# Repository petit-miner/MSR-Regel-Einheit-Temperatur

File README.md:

# MSR-Regel-Einheit-Temperatur
Dieses Projekt entstand in der Technik / µC AG des CRBK. Die Aufgabe war es die Temperatur eines Schaltschrankes zu überwachen und ggf. mit einem Lüfter zu kühlen. <br>
Diese Platine bietet die Möglichkeit die gemessen Temperaturen auf einer micro SD Karte zu loggen und auch per Ethernet entweder als Webserver oder als Client die gemessenen Daten bereitzustellen.<br> Die RTC sorgt beim Loggen für eine ständig korrekte Zeit.<br>
Es können bis zu 8 Onewire Sensoren, 3 PC-Lüfter und 2 normale Lüfter an die Platine angeschlossen werden.
<br>
<br>
Die Gerber Dateien und der Schaltplan wurden unter der Open Source Hardware Lizenz veröffentlicht und dürfen für den nicht kommerziellen Zweck gerne weiter verwendet werden.
<br>
<br>
Dieses Projekt wurde von Marcel Thürmer, Justin Wellenberg, Julian Prochowicz und Till Flesch entwickelt.

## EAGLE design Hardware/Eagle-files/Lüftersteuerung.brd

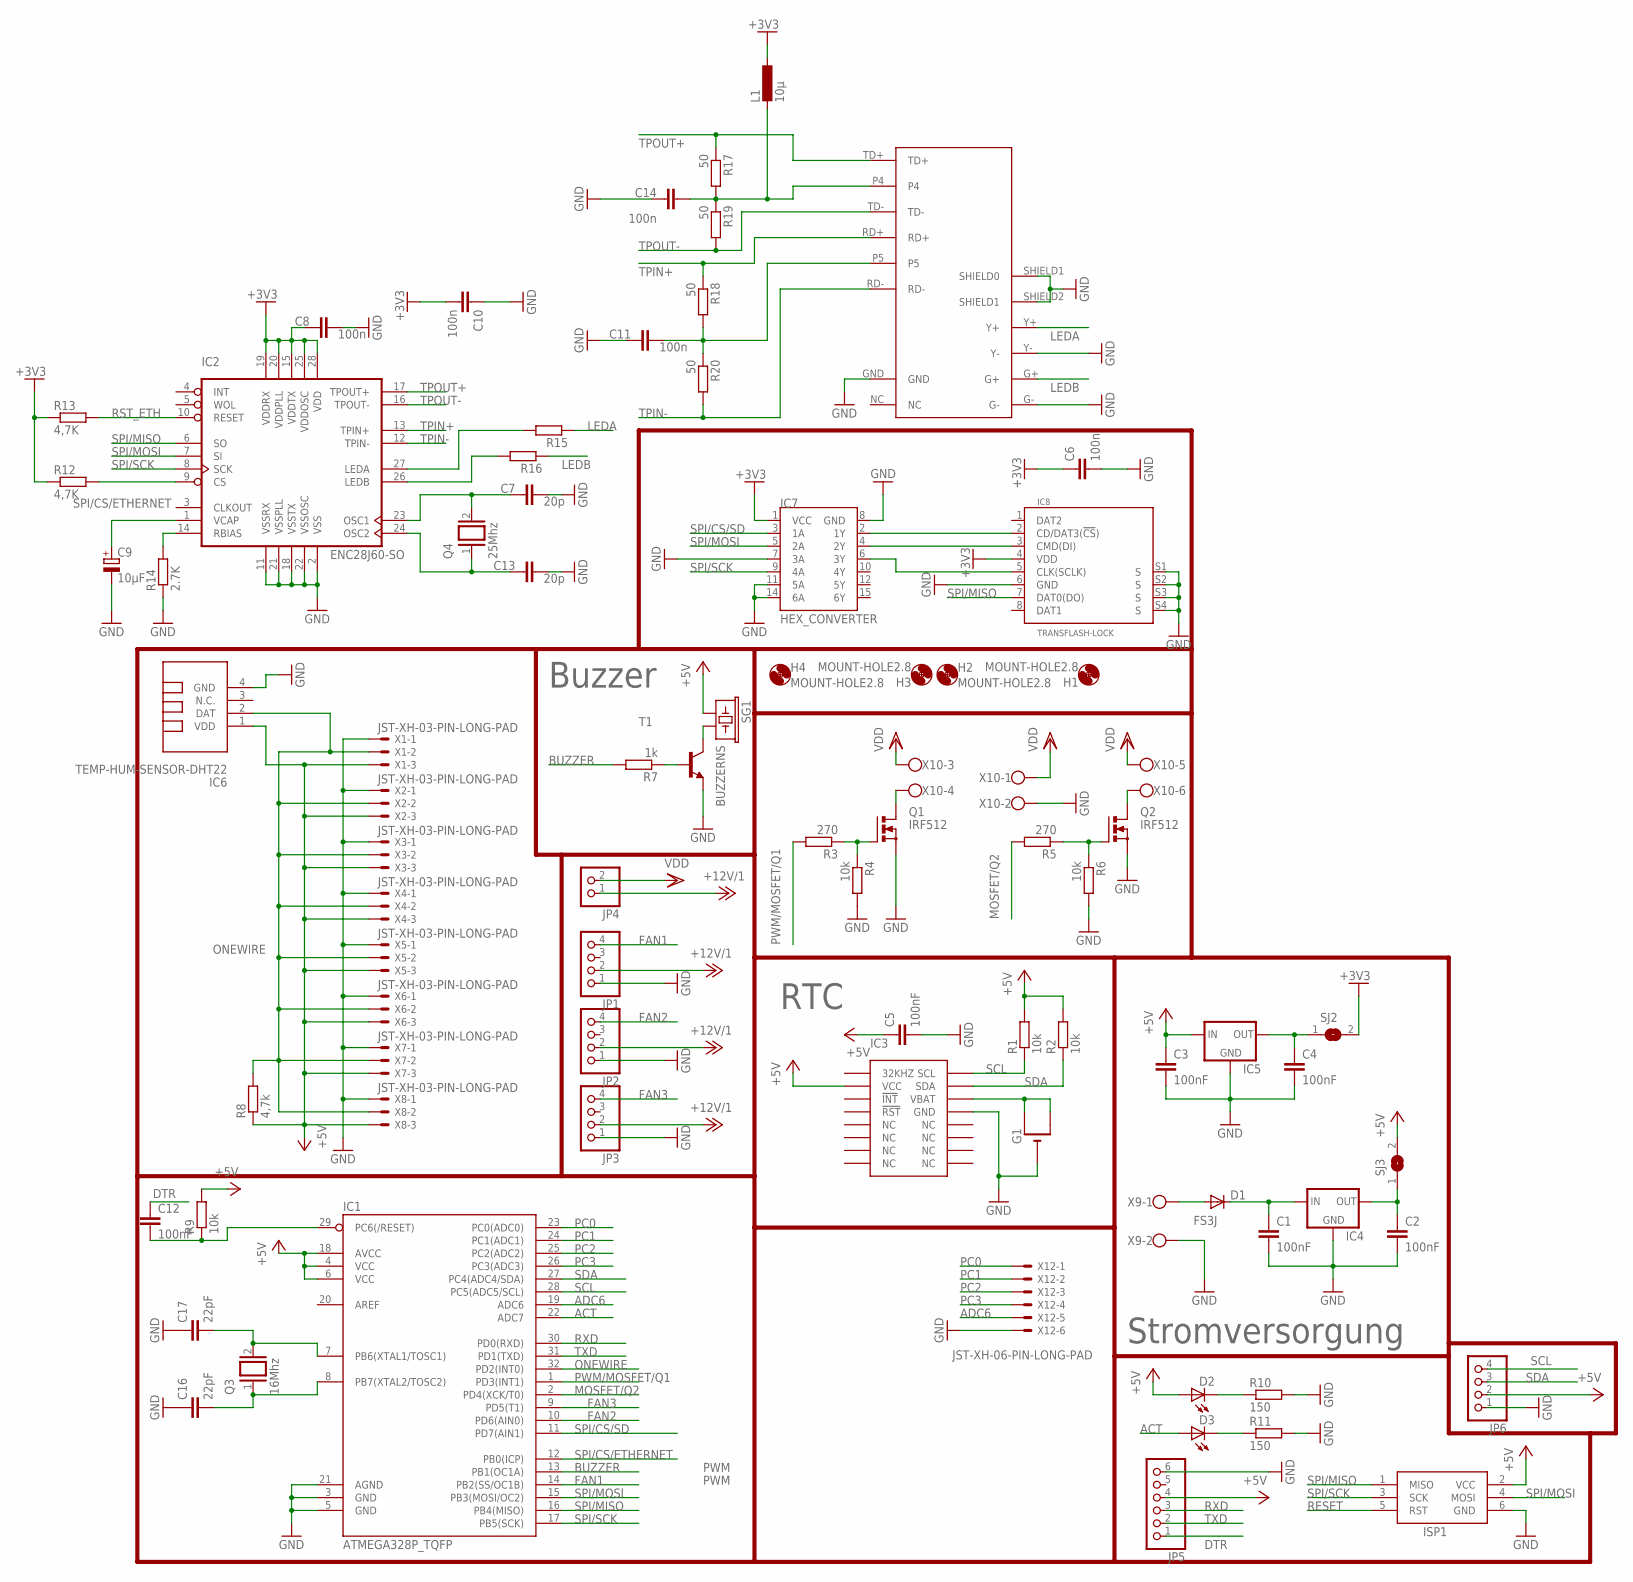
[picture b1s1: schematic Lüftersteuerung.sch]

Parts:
C1, C2, C3, C4, C5: 100nF; C1206
C6, C8, C10, C11, C14: 100n; C1206
C7, C13: 20p; C1206
C9: 10µF; A/3216-18W
C12: 100nF; C1206K
C16, C17: 22pF; C1206K
D1: FS3J; SMC
D2, D3: LED3MM
G1: CR1220SMT; CR1220-SMD
H1, H2, H3, H4: MOUNT-HOLE2.8; 2,8
IC1: ATMEGA328P_TQFP; TQFP32-08
IC2: ENC28J60-SO; SO28W
IC3: DS3231SOIC-16W; SOIC-16W
IC4, IC5: LM1117; SOT223
IC6: TEMP-HUM-SENSOR-DHT22
IC7: HEX_CONVERTER; SO016
IC8: TRANSFLASH-LOCK; TRANSFLASH-LOCK-SOCK
ISP1: AVRISP-6; AVRISP
JP1, JP2, JP3, JP6: PINHD-1X4; 1X04
JP4: PINHD-1X2; 1X02
JP5: PINHD-1X6; 1X06
L1: 10µ; L0805
Q1, Q2: IRF512; TO220BV
Q3: 16Mhz; QS
Q4: 25Mhz; QS
R1, R2, R4, R6: 10k; R1206
R3, R5: 270; R1206
R7: 1k; R1206
R8: 4,7k; R1206
R9: 10k; M1206
R10, R11: 150; M1206
R12, R13: 4,7K; R1206
R14: 2.7K; R1206
R15, R16: R-EU_R1206; R1206
R17, R18, R19, R20: 50; R1206
SG1: BUZZERNS; BUZZER-12MM-NS
SJ2, SJ3: SJ
T1: BC817-16-NPN-SOT23-BEC; SOT23-BEC
U$1: HR911105A; RJ45
X1, X2, X3, X4, X5, X6, X7, X8: JST-XH-03-PIN-LONG-PAD; JST-XH-03-PACKAGE-LONG-PAD
X9: W237-102
X10: W237-6
X12: JST-XH-06-PIN-LONG-PAD; JST-XH-06-PACKAGE-LONG-PAD

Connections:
+3V3: C6.1, C8.1, C10.2, IC2.15 (VDDTX), IC2.19 (VDDRX), IC2.20 (VDDPLL), IC2.25 (VDDOSC), IC2.28 (VDD), IC7.1 (VCC), IC8.4 (VDD), L1.1, R12.1, R13.1, SJ2.2
+5V: C3.1, C5.1, D2.A, IC1.4 (VCC), IC1.6 (VCC), IC1.18 (AVCC), IC3.2 (VCC), IC5.3 (IN), IC6.1 (VDD), ISP1.2 (VCC), JP5.4, JP6.2, R1.2, R2.2, R8.1, R9.2, SG1.+ (1), SJ3.2, X1.3, X2.3, X3.3, X4.3, X5.3, X6.3, X7.3, X8.3
+12V/1: JP1.2, JP2.2, JP3.2, JP4.1
ACT: D3.A, IC1.22 (ADC7)
ADC6: IC1.19 (ADC6), X12.5
BUZZER: IC1.13 (PB1(OC1A)), R7.2
DTR: C12.1, JP5.1
FAN1: IC1.14 (PB2(SS/OC1B)), JP1.4
FAN2: IC1.10 (PD6(AIN0)), JP2.4
FAN3: IC1.9 (PD5(T1)), JP3.4
GND: C1.2, C2.2, C3.2, C4.2, C5.2, C6.2, C7.2, C8.2, C9.-, C10.1, C11.1, C13.1, C14.1, C16.1, C17.1, G1.-, IC1.3 (GND), IC1.5 (GND), IC1.21 (AGND), IC2.2 (VSS), IC2.11 (VSSRX), IC2.18 (VSSTX), IC2.21 (VSSPLL), IC2.22 (VSSOSC), IC3.13 (GND), IC4.1 (GND), IC5.1 (GND), IC6.4 (GND), IC7.7 (3A), IC7.8 (GND), IC7.11 (5A), IC7.14 (6A), IC8.6 (GND), IC8.S1 (S), IC8.S2 (S), IC8.S3 (S), IC8.S4 (S), ISP1.6 (GND), JP1.1, JP2.1, JP3.1, JP5.6, JP6.1, Q1.S, Q2.S, R4.2, R6.2, R10.2, R11.2, R14.1, T1.E, U$1.G-, U$1.GND, U$1.SHIELD1 (SHIELD0), U$1.SHIELD2 (SHIELD1), U$1.Y-, X1.1, X2.1, X3.1, X4.1, X5.1, X6.1, X7.1, X8.1, X9.2, X10.2, X12.6
LEDA: R15.1, U$1.Y+
LEDB: R16.1, U$1.G+
MOSFET/Q2: IC1.2 (PD4(XCK/T0)), R5.2
unnamed: D1.A, X9.1
unnamed: C1.1, D1.C, IC4.3 (IN)
unnamed: C2.1, IC4.2 (OUT), SJ3.1
unnamed: G1.+$1 (+), G1.+$2 (+1), IC3.14 (VBAT)
unnamed: Q1.D, X10.4
unnamed: Q1.G, R3.1, R4.1
unnamed: Q2.D, X10.6
unnamed: SG1.- (2), T1.C
unnamed: Q2.G, R5.1, R6.1
unnamed: R7.1, T1.B
unnamed: C16.2, IC1.8 (PB7(XTAL2/TOSC2)), Q3.1
unnamed: C17.2, IC1.7 (PB6(XTAL1/TOSC1)), Q3.2
unnamed: D2.K (C), R10.1
unnamed: D3.K (C), R11.1
unnamed: IC7.2 (1Y), IC8.2 (CD/DAT3(!CS!))
unnamed: IC7.4 (2Y), IC8.3 (CMD(DI))
unnamed: IC7.6 (3Y), IC8.5 (CLK(SCLK))
unnamed: C13.2, IC2.24 (OSC2), Q4.1
unnamed: IC2.14 (RBIAS), R14.2
unnamed: C7.1, IC2.23 (OSC1), Q4.2
unnamed: C9.+, IC2.1 (VCAP)
unnamed: C14.2, L1.2, R17.2, R19.1, U$1.P4
unnamed: IC2.26 (LEDB), R16.2
unnamed: IC2.27 (LEDA), R15.2
unnamed: C11.2, R18.2, R20.1, U$1.P5
unnamed: C4.1, IC5.2 (OUT), SJ2.1
ONEWIRE: IC1.32 (PD2(INT0)), IC6.2 (DAT), R8.2, X1.2, X2.2, X3.2, X4.2, X5.2, X6.2, X7.2, X8.2
PC0: IC1.23 (PC0(ADC0)), X12.1
PC1: IC1.24 (PC1(ADC1)), X12.2
PC2: IC1.25 (PC2(ADC2)), X12.3
PC3: IC1.26 (PC3(ADC3)), X12.4
PWM/MOSFET/Q1: IC1.1 (PD3(INT1)), R3.2
RESET: C12.2, IC1.29 (PC6(/RESET)), ISP1.5 (RST), R9.1
RST_ETH: IC2.10 (RESET), R13.2
RXD: IC1.30 (PD0(RXD)), JP5.3
SCL: IC1.28 (PC5(ADC5/SCL)), IC3.16 (SCL), JP6.4, R1.1
SDA: IC1.27 (PC4(ADC4/SDA)), IC3.15 (SDA), JP6.3, R2.1
SPI/CS/ETHERNET: IC1.12 (PB0(ICP)), IC2.9 (CS), R12.2
SPI/CS/SD: IC1.11 (PD7(AIN1)), IC7.3 (1A)
SPI/MISO: IC1.16 (PB4(MISO)), IC2.6 (SO), IC8.7 (DAT0(DO)), ISP1.1 (MISO)
SPI/MOSI: IC1.15 (PB3(MOSI/OC2)), IC2.7 (SI), IC7.5 (2A), ISP1.4 (MOSI)
SPI/SCK: IC1.17 (PB5(SCK)), IC2.8 (SCK), IC7.9 (4A), ISP1.3 (SCK)
TPIN+: IC2.13 (TPIN+), R18.1, U$1.RD+
TPIN-: IC2.12 (TPIN-), R20.2, U$1.RD-
TPOUT+: IC2.17 (TPOUT+), R17.1, U$1.TD+
TPOUT-: IC2.16 (TPOUT-), R19.2, U$1.TD-
TXD: IC1.31 (PD1(TXD)), JP5.2
VDD: JP4.2, X10.1, X10.3, X10.5

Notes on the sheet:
Stromversorgung
PWM
RTC
Buzzer

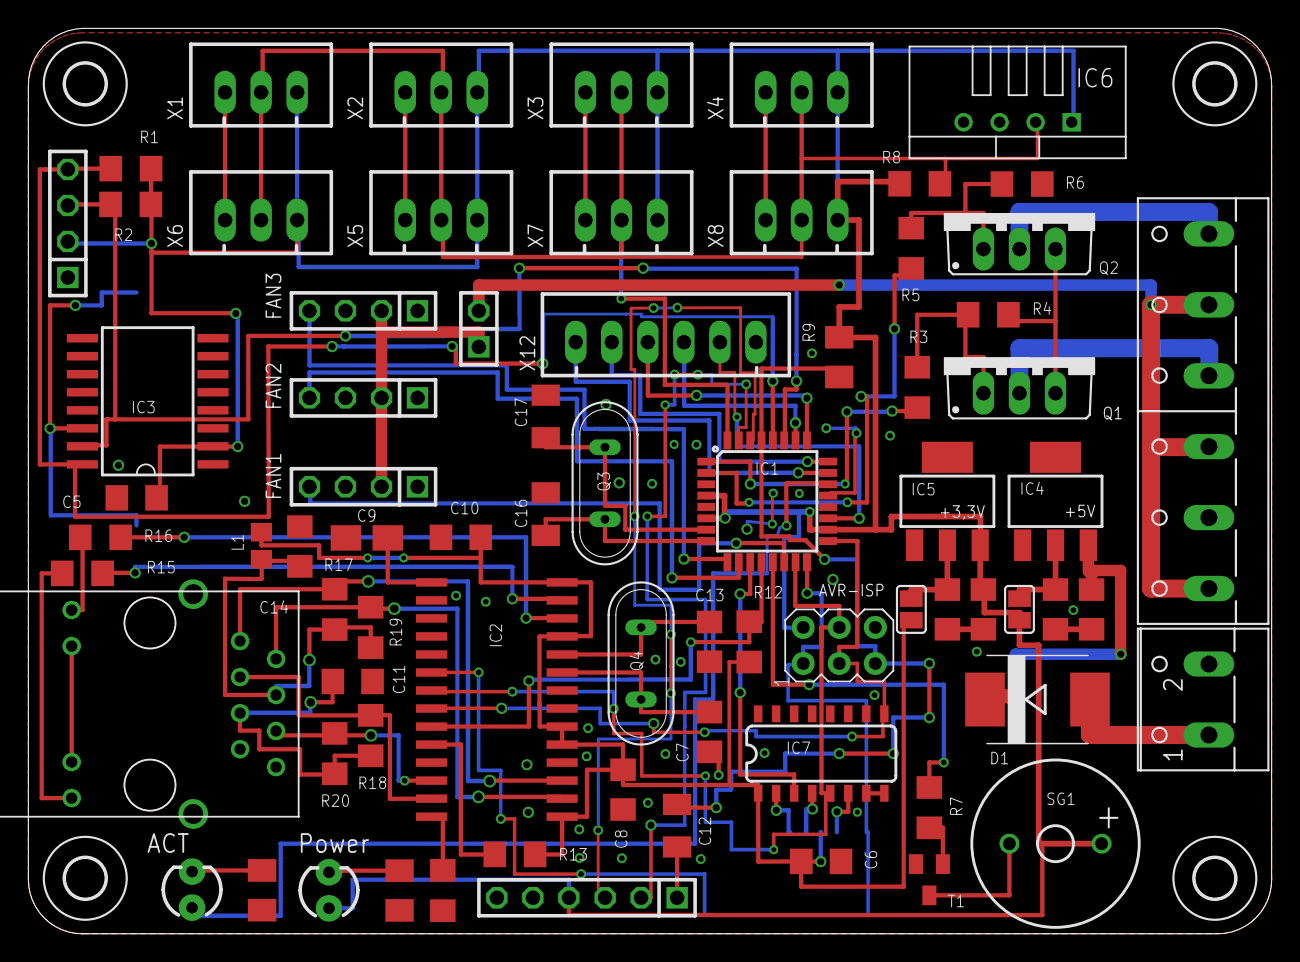
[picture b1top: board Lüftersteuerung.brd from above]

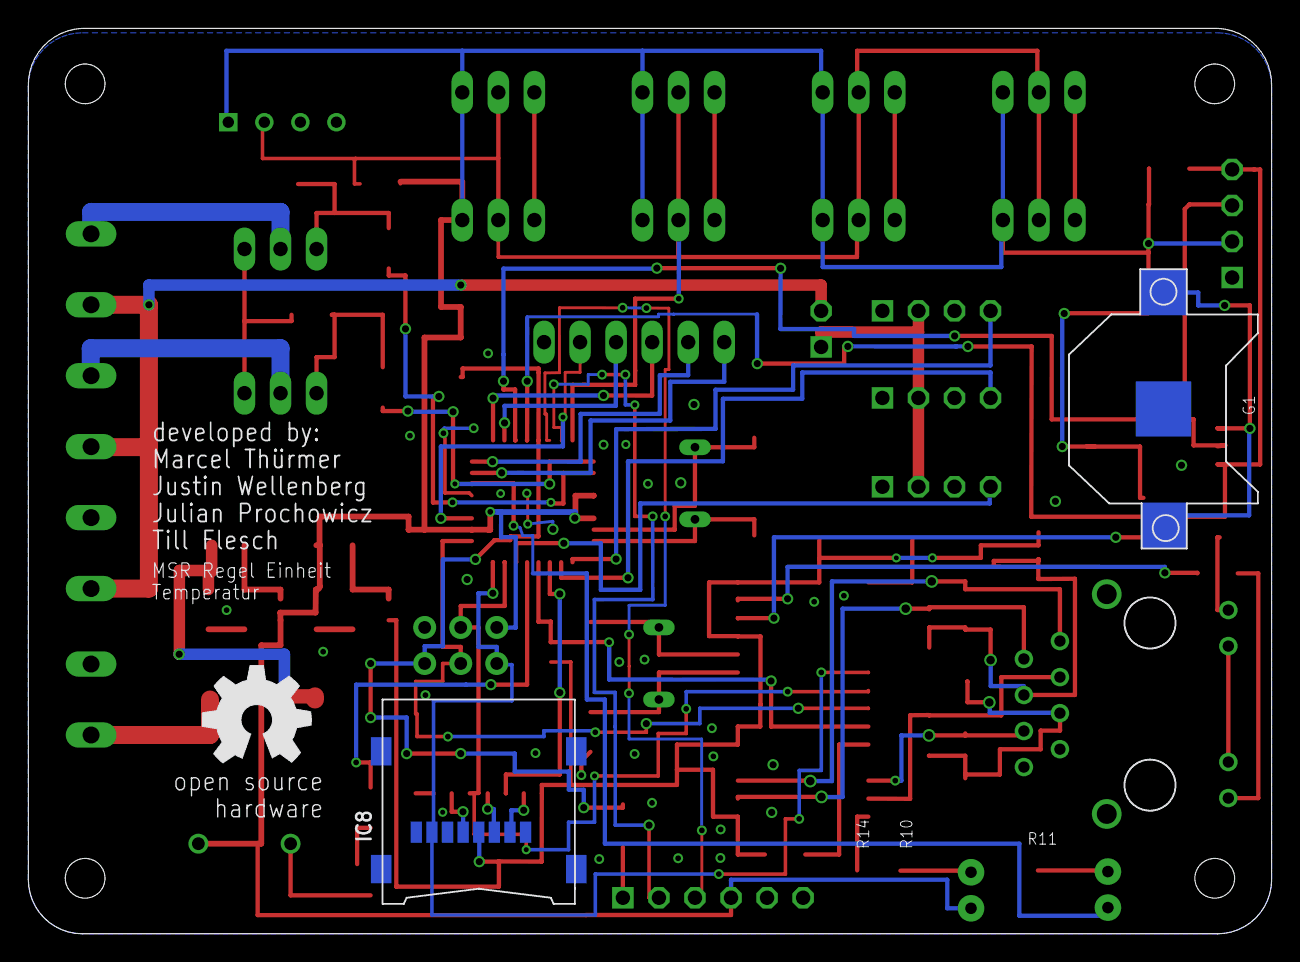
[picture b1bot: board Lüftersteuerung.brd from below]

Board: 2 copper layers, 87.5 x 63.7 mm, 81 parts (3 on the bottom side), 62 nets.

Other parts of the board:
U$2: OSHW_8MM

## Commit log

2017-05-29 Added folder Hardware
2017-05-29 Added photos of the pcb
2017-09-12 added developer names

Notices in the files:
parts and their libraries:
SparkFun-IC-Microcontroller: Licensing: Creative Commons ShareAlike 4.0 International - https://creativecommons.org/licenses/by-sa/4.0
diy-modules: Released under the Creative Commons Attribution 4.0 International License: http://creativecommons.org/licenses/by/4.0
